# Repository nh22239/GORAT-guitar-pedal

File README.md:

# GORAT RAT clone 
Here at **GORAM** industries, we love the sound of a good dirty **RAT**, but what if we all want to use one at the same time? Suffice to say, we'd probably all get lost in eachothers sound.
That's why we've decided to go custom, a brand new **RAT** clone built by **GORAM**, for **GORAM**.

## New features:
### Frequency response selector switch!

  A simple knob that allows switching the filters of the op-amp stage between **Regular**, **Bass**, and **BEANS** modes
  
### Diode selector switch

  Pick between 6 different diode combinations
  1. BAT41 - BAT 41
  2. Red LED - Red LED 
  3. 1N914 - 1N914
  4. 1N914 - Open
  5. BAT41 - 1N914
  6. BAT41 - Red LED

### Wet/Dry knob
  Does what it says on the tin, for when the un-adulterated bass tone needs to shine through a bit more.

## Future Features:
### Diode selector gain compensation
  When switching diodes, also switch feedback resistor on a compensation op-amp.
### SMD components
  The enclosure is very busy, any new features would probably require this.
### Mini versions
  Much smaller package sizes individualised for Bass, Standard, and Beans.
### Colour LED display
  Switch between red, green, and blue when the feedback capacitor selector is changed, easy to implement as the 4x3 rotarty switch has a free pole but version 1.1 has run out of board space.

## Update 24/03/2026
The PCB's have arrived!
Due to the different heights of components, not to mention mechanical strain, I've designed the board to be printed as one piece that snaps off into three. The intention is that the breakout for the stomp button, and having flying wires for all of the jacks, will reduce the wear on the piece and contribute to a more professional finish.

<?xml version="1.0" encoding="UTF-8" standalone="no"?>
<!-- Created with Inkscape (http://www.inkscape.org/) -->

<svg
   width="210mm"
   height="297mm"
   viewBox="0 0 210 297"
   version="1.1"
   id="svg1"
   xml:space="preserve"
   inkscape:version="1.4.2 (ebf0e94, 2025-05-08)"
   sodipodi:docname="LineDrawing.svg"
   xmlns:inkscape="http://www.inkscape.org/namespaces/inkscape"
   xmlns:sodipodi="http://sodipodi.sourceforge.net/DTD/sodipodi-0.dtd"
   xmlns="http://www.w3.org/2000/svg"
   xmlns:svg="http://www.w3.org/2000/svg"><sodipodi:namedview
     id="namedview1"
     pagecolor="#ffffff"
     bordercolor="#000000"
     borderopacity="0.25"
     inkscape:showpageshadow="2"
     inkscape:pageopacity="0.0"
     inkscape:pagecheckerboard="0"
     inkscape:deskcolor="#d1d1d1"
     inkscape:document-units="mm"
     inkscape:zoom="0.68862935"
     inkscape:cx="238.15424"
     inkscape:cy="382.64416"
     inkscape:window-width="1920"
     inkscape:window-height="991"
     inkscape:window-x="3191"
     inkscape:window-y="435"
     inkscape:window-maximized="1"
     inkscape:current-layer="layer1" /><defs
     id="defs1"><rect
       x="546.73824"
       y="238.45997"
       width="66.79936"
       height="36.65103"
       id="rect40" /><marker
       id="DistanceX"
       orient="auto"
       refX="0.0"
       refY="0.0"
       style="overflow:visible"><path
         d="M 3,-3 L -3,3 M 0,-5 L  0,5"
         style="stroke:#000000; stroke-width:0.5"
         id="path1" /></marker><pattern
       id="Hatch"
       patternUnits="userSpaceOnUse"
       width="8"
       height="8"
       x="0"
       y="0"><path
         d="M8 4 l-4,4"
         stroke="#000000"
         stroke-width="0.25"
         linecap="square"
         id="path2" /><path
         d="M6 2 l-4,4"
         stroke="#000000"
         stroke-width="0.25"
         linecap="square"
         id="path3" /><path
         d="M4 0 l-4,4"
         stroke="#000000"
         stroke-width="0.25"
         linecap="square"
         id="path4" /></pattern><symbol
       id="*MODEL_SPACE" /><symbol
       id="*PAPER_SPACE" /><marker
       id="DistanceX-0"
       orient="auto"
       refX="0.0"
       refY="0.0"
       style="overflow:visible"><path
         d="M 3,-3 L -3,3 M 0,-5 L  0,5"
         style="stroke:#000000; stroke-width:0.5"
         id="path1-9" /></marker><pattern
       id="Hatch-4"
       patternUnits="userSpaceOnUse"
       width="8"
       height="8"
       x="0"
       y="0"><path
         d="M8 4 l-4,4"
         stroke="#000000"
         stroke-width="0.25"
         linecap="square"
         id="path2-8" /><path
         d="M6 2 l-4,4"
         stroke="#000000"
         stroke-width="0.25"
         linecap="square"
         id="path3-8" /><path
         d="M4 0 l-4,4"
         stroke="#000000"
         stroke-width="0.25"
         linecap="square"
         id="path4-2" /></pattern><symbol
       id="*MODEL_SPACE-4" /><symbol
       id="*PAPER_SPACE-5" /><marker
       id="DistanceX-1"
       orient="auto"
       refX="0.0"
       refY="0.0"
       style="overflow:visible"><path
         d="M 3,-3 L -3,3 M 0,-5 L  0,5"
         style="stroke:#000000; stroke-width:0.5"
         id="path1-4" /></marker><pattern
       id="Hatch-2"
       patternUnits="userSpaceOnUse"
       width="8"
       height="8"
       x="0"
       y="0"><path
         d="M8 4 l-4,4"
         stroke="#000000"
         stroke-width="0.25"
         linecap="square"
         id="path2-3" /><path
         d="M6 2 l-4,4"
         stroke="#000000"
         stroke-width="0.25"
         linecap="square"
         id="path3-2" /><path
         d="M4 0 l-4,4"
         stroke="#000000"
         stroke-width="0.25"
         linecap="square"
         id="path4-21" /></pattern><symbol
       id="*MODEL_SPACE-6" /><symbol
       id="*PAPER_SPACE-8" /></defs><g
     inkscape:label="Layer 1"
     inkscape:groupmode="layer"
     id="layer1"><g
       inkscape:label="0"
       id="g13"
       transform="matrix(0.26458333,0,0,-0.26458333,173.01219,290.36032)"><path
         d="m -353.42983,925.10662 a 17.007875,17.007875 0 0 0 -34.01575,0 17.007875,17.007875 0 0 0 34.01575,0 z"
         style="fill:none;stroke:#000000"
         id="path5" /><path
         d="m -211.98102,921.32712 a 26.173228,26.173228 0 0 0 -52.34645,0 26.173228,26.173228 0 0 0 52.34645,0 z"
         style="fill:none;stroke:#000000"
         id="path6" /><path
         d="m -88.862904,925.10662 a 17.007875,17.007875 0 0 0 -34.015746,0 17.007875,17.007875 0 0 0 34.015746,0 z"
         style="fill:none;stroke:#000000"
         id="path7" /><path
         d="M -450.75266,972.35072 H -25.555824 V 870.30342 H -450.75266 Z"
         style="fill:none;stroke:#000000"
         id="path8" /><path
         d="m -450.75266,870.30342 v -11.33855 h 425.196836 v 11.33855 z"
         style="fill:none;stroke:#000000"
         id="path9" /><path
         d="m -450.75266,870.30342 h -11.33859 v 102.0473 h 11.33859 z"
         style="fill:none;stroke:#000000"
         id="path10" /><path
         d="m -450.75266,858.96487 a 11.338583,11.338583 0 0 0 -11.33859,11.33855 h 11.33859 z"
         style="fill:none;stroke:#000000"
         id="path11" /><path
         d="m -25.555824,972.35072 h 11.33859 v -102.0473 h -11.33859 z"
         style="fill:none;stroke:#000000"
         id="path12" /><path
         d="m -25.555824,870.30342 v -11.33855 a 11.338583,11.338583 0 0 1 11.33859,11.33855 z"
         style="fill:none;stroke:#000000"
         id="path13" /></g><g
       inkscape:label="0"
       id="g22"
       transform="matrix(0.26458333,0,0,0.26458333,108.07374,-177.71021)"><path
         d="m 73.322835,1029.8731 a 13.6063,13.6063 0 0 0 -27.212599,0 13.6063,13.6063 0 0 0 27.212599,0 z"
         style="fill:none;stroke:#000000"
         id="path5-5" /><path
         d="m -30.614173,1216.586 a 17.76378,17.76378 0 0 0 -35.527559,0 17.76378,17.76378 0 0 0 35.527559,0 z"
         style="fill:none;stroke:#000000"
         id="path6-1" /><path
         d="m 49.020472,1238.692 a 9.448819,9.448819 0 0 0 -18.897637,0 9.448819,9.448819 0 0 0 18.897637,0 z"
         style="fill:none;stroke:#000000"
         id="path7-7" /><path
         d="m -46.299213,1029.8731 a 13.606299,13.606299 0 0 0 -27.212598,0 13.606299,13.606299 0 0 0 27.212598,0 z"
         style="fill:none;stroke:#000000"
         id="path8-1" /><path
         d="m 192.94488,1028.9283 a 13.6063,13.6063 0 0 0 -27.2126,0 13.6063,13.6063 0 0 0 27.2126,0 z"
         style="fill:none;stroke:#000000"
         id="path9-1" /><path
         d="m -133.36819,1216.586 a 17.76378,17.76378 0 0 0 -35.52756,0 17.76378,17.76378 0 0 0 35.52756,0 z"
         style="fill:none;stroke:#000000"
         id="path10-5" /><path
         d="m 172.40073,1236.0464 a 24.999155,24.999155 0 0 0 -49.99831,0 24.999155,24.999155 0 0 0 49.99831,0 z"
         style="fill:none;stroke:#000000"
         id="path11-2" /><path
         d="m -165.92126,1029.8731 a 13.6063,13.6063 0 0 0 -27.2126,0 13.6063,13.6063 0 0 0 27.2126,0 z"
         style="fill:none;stroke:#000000"
         id="path12-7" /><path
         d="M 212.59842,958.11024 H -212.59842 V 1286.9291 H 212.59842 Z"
         style="fill:none;stroke:#000000"
         id="path13-6" /><path
         d="m 212.59842,946.77165 v 11.33859 h -425.19684 v -11.33859 z"
         style="fill:none;stroke:#000000"
         id="path14" /><path
         d="m -212.59842,946.77165 v 11.33859 h -11.33859 a 11.338583,11.338583 0 0 1 11.33859,-11.33859 z"
         style="fill:none;stroke:#000000"
         id="path15" /><path
         d="m -223.93701,958.11024 h 11.33859 v 328.81886 h -11.33859 z"
         style="fill:none;stroke:#000000"
         id="path16" /><path
         d="m 212.59842,1286.9291 v 11.3386 h -425.19684 v -11.3386 z"
         style="fill:none;stroke:#000000"
         id="path17" /><path
         d="m -212.59842,1286.9291 v 11.3386 a 11.338583,11.338583 0 0 1 -11.33859,-11.3386 z"
         style="fill:none;stroke:#000000"
         id="path18" /><path
         d="m 212.59842,958.11024 h 11.33859 v 328.81886 h -11.33859 z"
         style="fill:none;stroke:#000000"
         id="path19" /><path
         d="m 212.59842,1298.2677 a 11.338583,11.338583 0 0 0 11.33859,-11.3386 h -11.33859 z"
         style="fill:none;stroke:#000000"
         id="path20" /><path
         style="fill:none;stroke:#000000"
         d="M 212.598,946.772 V 958.11"
         id="path21" /><path
         d="m 212.59842,958.11024 h 11.33859 a 11.338583,11.338583 0 0 0 -11.33859,-11.33859 z"
         style="fill:none;stroke:#000000"
         id="path22" /></g><g
       inkscape:label="0"
       id="g10"
       transform="matrix(0,-0.26458333,-0.26458333,0,308.48541,119.99916)"><path
         d="m -164.40945,1107.4016 h 328.8189 v -102.0473 h -328.8189 z"
         style="fill:none;stroke:#000000"
         id="path5-57" /><path
         d="m -164.40945,1005.3543 v -11.33855 h 328.8189 v 11.33855 z"
         style="fill:none;stroke:#000000"
         id="path6-6" /><path
         d="m -164.40945,994.01575 a 11.338583,11.338583 0 0 0 -11.33858,11.33855 h 11.33858 z"
         style="fill:none;stroke:#000000"
         id="path7-1" /><path
         d="m -175.74803,1107.4016 h 11.33858 v -102.0473 h -11.33858 z"
         style="fill:none;stroke:#000000"
         id="path8-8" /><path
         d="m 175.74803,1005.3543 a 11.338583,11.338583 0 0 0 -11.33858,-11.33855 v 11.33855 z"
         style="fill:none;stroke:#000000"
         id="path9-9" /><path
         d="m 164.40945,1107.4016 h 11.33858 v -102.0473 h -11.33858 z"
         style="fill:none;stroke:#000000"
         id="path10-2" /></g><g
       inkscape:label="0"
       id="g28"
       transform="matrix(0,0.26458333,0.26458333,0,-92.15514,118.58116)"><path
         d="m -164.40945,1107.4016 h 328.8189 v -102.0473 h -328.8189 z"
         style="fill:none;stroke:#000000"
         id="path23" /><path
         d="m -164.40945,1005.3543 v -11.33855 h 328.8189 v 11.33855 z"
         style="fill:none;stroke:#000000"
         id="path24" /><path
         d="m -164.40945,994.01575 a 11.338583,11.338583 0 0 0 -11.33858,11.33855 h 11.33858 z"
         style="fill:none;stroke:#000000"
         id="path25" /><path
         d="m -175.74803,1107.4016 h 11.33858 v -102.0473 h -11.33858 z"
         style="fill:none;stroke:#000000"
         id="path26" /><path
         d="m 175.74803,1005.3543 a 11.338583,11.338583 0 0 0 -11.33858,-11.33855 v 11.33855 z"
         style="fill:none;stroke:#000000"
         id="path27" /><path
         d="m 164.40945,1107.4016 h 11.33858 v -102.0473 h -11.33858 z"
         style="fill:none;stroke:#000000"
         id="path28" /></g><g
       id="g37"
       transform="translate(0,8.4527814)"><path
         d="M 51.82946,206.78981 H 164.32945 V 179.7898 H 51.82946 Z"
         style="fill:none;stroke:#000000;stroke-width:0.264583"
         id="path32" /><path
         d="m 51.82946,179.7898 v -2.99999 h 112.49999 v 2.99999 z"
         style="fill:none;stroke:#000000;stroke-width:0.264583"
         id="path33" /><path
         d="m 51.82946,179.7898 h -3.000002 v 27.00001 h 3.000002 z"
         style="fill:none;stroke:#000000;stroke-width:0.264583"
         id="path34" /><path
         d="m 51.82946,176.78981 a 3,3 0 0 0 -3.000002,2.99999 h 3.000002 z"
         style="fill:none;stroke:#000000;stroke-width:0.264583"
         id="path35" /><path
         d="m 164.32945,206.78981 h 3.00001 V 179.7898 h -3.00001 z"
         style="fill:none;stroke:#000000;stroke-width:0.264583"
         id="path36" /><path
         d="m 164.32945,179.7898 v -2.99999 a 3,3 0 0 1 3.00001,2.99999 z"
         style="fill:none;stroke:#000000;stroke-width:0.264583"
         id="path37" /></g><text
       xml:space="preserve"
       style="font-size:4.9389px;line-height:1;font-family:Typewriter-Serial;-inkscape-font-specification:'Typewriter-Serial, Normal';text-align:center;writing-mode:lr-tb;direction:ltr;text-anchor:middle;white-space:pre;inline-size:24.3507;fill:#000000;stroke-width:0.365001;stroke-linejoin:round;paint-order:markers stroke fill"
       x="51.823742"
       y="72.78978"
       id="text37"
       transform="translate(7.6071151,-2.7168268)"><tspan
         x="51.823742"
         y="72.78978"
         id="tspan2"><tspan
           style="stroke-width:0.365"
           id="tspan1">Gain</tspan></tspan></text><text
       xml:space="preserve"
       style="font-size:4.9389px;line-height:1;font-family:Typewriter-Serial;-inkscape-font-specification:'Typewriter-Serial, Normal';text-align:center;writing-mode:lr-tb;direction:ltr;text-anchor:middle;white-space:pre;inline-size:24.3507;fill:#000000;stroke-width:0.365001;stroke-linejoin:round;paint-order:markers stroke fill"
       x="51.823742"
       y="72.78978"
       id="text38"
       transform="translate(39.937354,-2.9885095)"><tspan
         x="51.823742"
         y="72.78978"
         id="tspan4"><tspan
           style="stroke-width:0.365"
           id="tspan3">Filter</tspan></tspan></text><text
       xml:space="preserve"
       style="font-size:4.9389px;line-height:1;font-family:Typewriter-Serial;-inkscape-font-specification:'Typewriter-Serial, Normal';text-align:center;writing-mode:lr-tb;direction:ltr;text-anchor:middle;white-space:pre;inline-size:24.3507;fill:#000000;stroke-width:0.365001;stroke-linejoin:round;paint-order:markers stroke fill"
       x="51.823742"
       y="72.78978"
       id="text39"
       transform="translate(71.251067,-3.3727268)"><tspan
         x="51.823742"
         y="72.78978"
         id="tspan6"><tspan
           style="stroke-width:0.365"
           id="tspan5">Volume</tspan></tspan></text><text
       xml:space="preserve"
       transform="scale(0.26458333)"
       id="text40"
       style="text-orientation:auto;stroke-linejoin:round;-inkscape-font-specification:'Typewriter-Serial, Normal';font-family:Typewriter-Serial;font-size:18.66666667px;fill:#000000;line-height:1;paint-order:markers stroke fill;stroke-width:1.37952756;text-align:center;writing-mode:lr-tb;direction:ltr;white-space:pre;shape-inside:url(#rect40)" /><text
       xml:space="preserve"
       style="font-size:4.9389px;line-height:1;font-family:Typewriter-Serial;-inkscape-font-specification:'Typewriter-Serial, Normal';text-align:center;writing-mode:lr-tb;direction:ltr;text-anchor:middle;white-space:pre;inline-size:24.3507;fill:#000000;stroke-width:0.365001;stroke-linejoin:round;paint-order:markers stroke fill"
       x="51.823742"
       y="72.78978"
       id="text41"
       transform="translate(102.37267,-3.3727268)"><tspan
         x="51.823742"
         y="72.78978"
         id="tspan8"><tspan
           style="stroke-width:0.365"
           id="tspan7">Wet/Dry</tspan></tspan></text><text
       xml:space="preserve"
       style="font-size:4.9389px;line-height:1;font-family:Typewriter-Serial;-inkscape-font-specification:'Typewriter-Serial, Normal';text-align:center;writing-mode:lr-tb;direction:ltr;text-anchor:middle;white-space:pre;inline-size:24.3507;fill:#000000;stroke-width:0.365001;stroke-linejoin:round;paint-order:markers stroke fill"
       x="51.823742"
       y="72.78978"
       id="text42"
       transform="translate(14.194792,99.213302)"><tspan
         x="51.823742"
         y="72.78978"
         id="tspan10"><tspan
           style="stroke-width:0.365"
           id="tspan9">Bass/</tspan></tspan><tspan
         x="51.823742"
         y="77.728687"
         id="tspan12"><tspan
           style="stroke-width:0.365"
           id="tspan11">Reg/</tspan></tspan><tspan
         x="51.823742"
         y="82.667591"
         id="tspan14"><tspan
           style="stroke-width:0.365"
           id="tspan13">Beans</tspan></tspan></text><text
       xml:space="preserve"
       style="font-size:4.9389px;line-height:1;font-family:Typewriter-Serial;-inkscape-font-specification:'Typewriter-Serial, Normal';text-align:center;writing-mode:lr-tb;direction:ltr;text-anchor:middle;white-space:pre;inline-size:24.3507;fill:#000000;stroke-width:0.365001;stroke-linejoin:round;paint-order:markers stroke fill"
       x="51.823742"
       y="72.78978"
       id="text43"
       transform="translate(43.011092,99.789628)"><tspan
         x="51.823742"
         y="72.78978"
         id="tspan16"><tspan
           style="stroke-width:0.365"
           id="tspan15">Diode</tspan><tspan
           y="72.78978"
           id="tspan17"> </tspan></tspan><tspan
         x="51.823742"
         y="77.728687"
         id="tspan19"><tspan
           style="stroke-width:0.365"
           id="tspan18">Selection</tspan></tspan></text><text
       xml:space="preserve"
       style="font-size:4.9389px;line-height:1;font-family:Typewriter-Serial;-inkscape-font-specification:'Typewriter-Serial, Normal';text-align:center;writing-mode:lr-tb;direction:ltr;text-anchor:middle;white-space:pre;inline-size:24.3507;fill:#000000;stroke-width:0.365001;stroke-linejoin:round;paint-order:markers stroke fill"
       x="51.823742"
       y="72.78978"
       id="text44"
       transform="translate(70.866849,99.789628)"><tspan
         x="51.823742"
         y="72.78978"
         id="tspan21"><tspan
           style="stroke-width:0.365"
           id="tspan20">LED</tspan></tspan></text><text
       xml:space="preserve"
       style="font-size:4.9389px;line-height:1;font-family:Typewriter-Serial;-inkscape-font-specification:'Typewriter-Serial, Normal';text-align:center;writing-mode:lr-tb;direction:ltr;text-anchor:middle;white-space:pre;inline-size:34.7246;fill:#000000;stroke-width:0.365001;stroke-linejoin:round;paint-order:markers stroke fill"
       x="51.823742"
       y="72.78978"
       id="text45"
       transform="translate(95.26465,102.47915)"><tspan
         x="51.823742"
         y="72.78978"
         id="tspan23"><tspan
           style="stroke-width:0.365"
           id="tspan22">Footswitch</tspan></tspan></text><text
       xml:space="preserve"
       style="font-size:4.9389px;line-height:1;font-family:Typewriter-Serial;-inkscape-font-specification:'Typewriter-Serial, Normal';text-align:center;writing-mode:lr-tb;direction:ltr;text-anchor:middle;white-space:pre;inline-size:34.7246;fill:#000000;stroke-width:0.365001;stroke-linejoin:round;paint-order:markers stroke fill"
       x="51.823742"
       y="72.78978"
       id="text46"
       transform="translate(96.108218,-44.483981)"><tspan
         x="51.823742"
         y="72.78978"
         id="tspan25"><tspan
           style="stroke-width:0.365"
           id="tspan24">In</tspan></tspan></text><text
       xml:space="preserve"
       style="font-size:4.9389px;line-height:1;font-family:Typewriter-Serial;-inkscape-font-specification:'Typewriter-Serial, Normal';text-align:center;writing-mode:lr-tb;direction:ltr;text-anchor:middle;white-space:pre;inline-size:34.7246;fill:#000000;stroke-width:0.365001;stroke-linejoin:round;paint-order:markers stroke fill"
       x="51.823742"
       y="72.78978"
       id="text47"
       transform="translate(22.914816,-46.02085)"><tspan
         x="51.823742"
         y="72.78978"
         id="tspan27"><tspan
           style="stroke-width:0.365"
           id="tspan26">Out</tspan></tspan></text></g></svg>

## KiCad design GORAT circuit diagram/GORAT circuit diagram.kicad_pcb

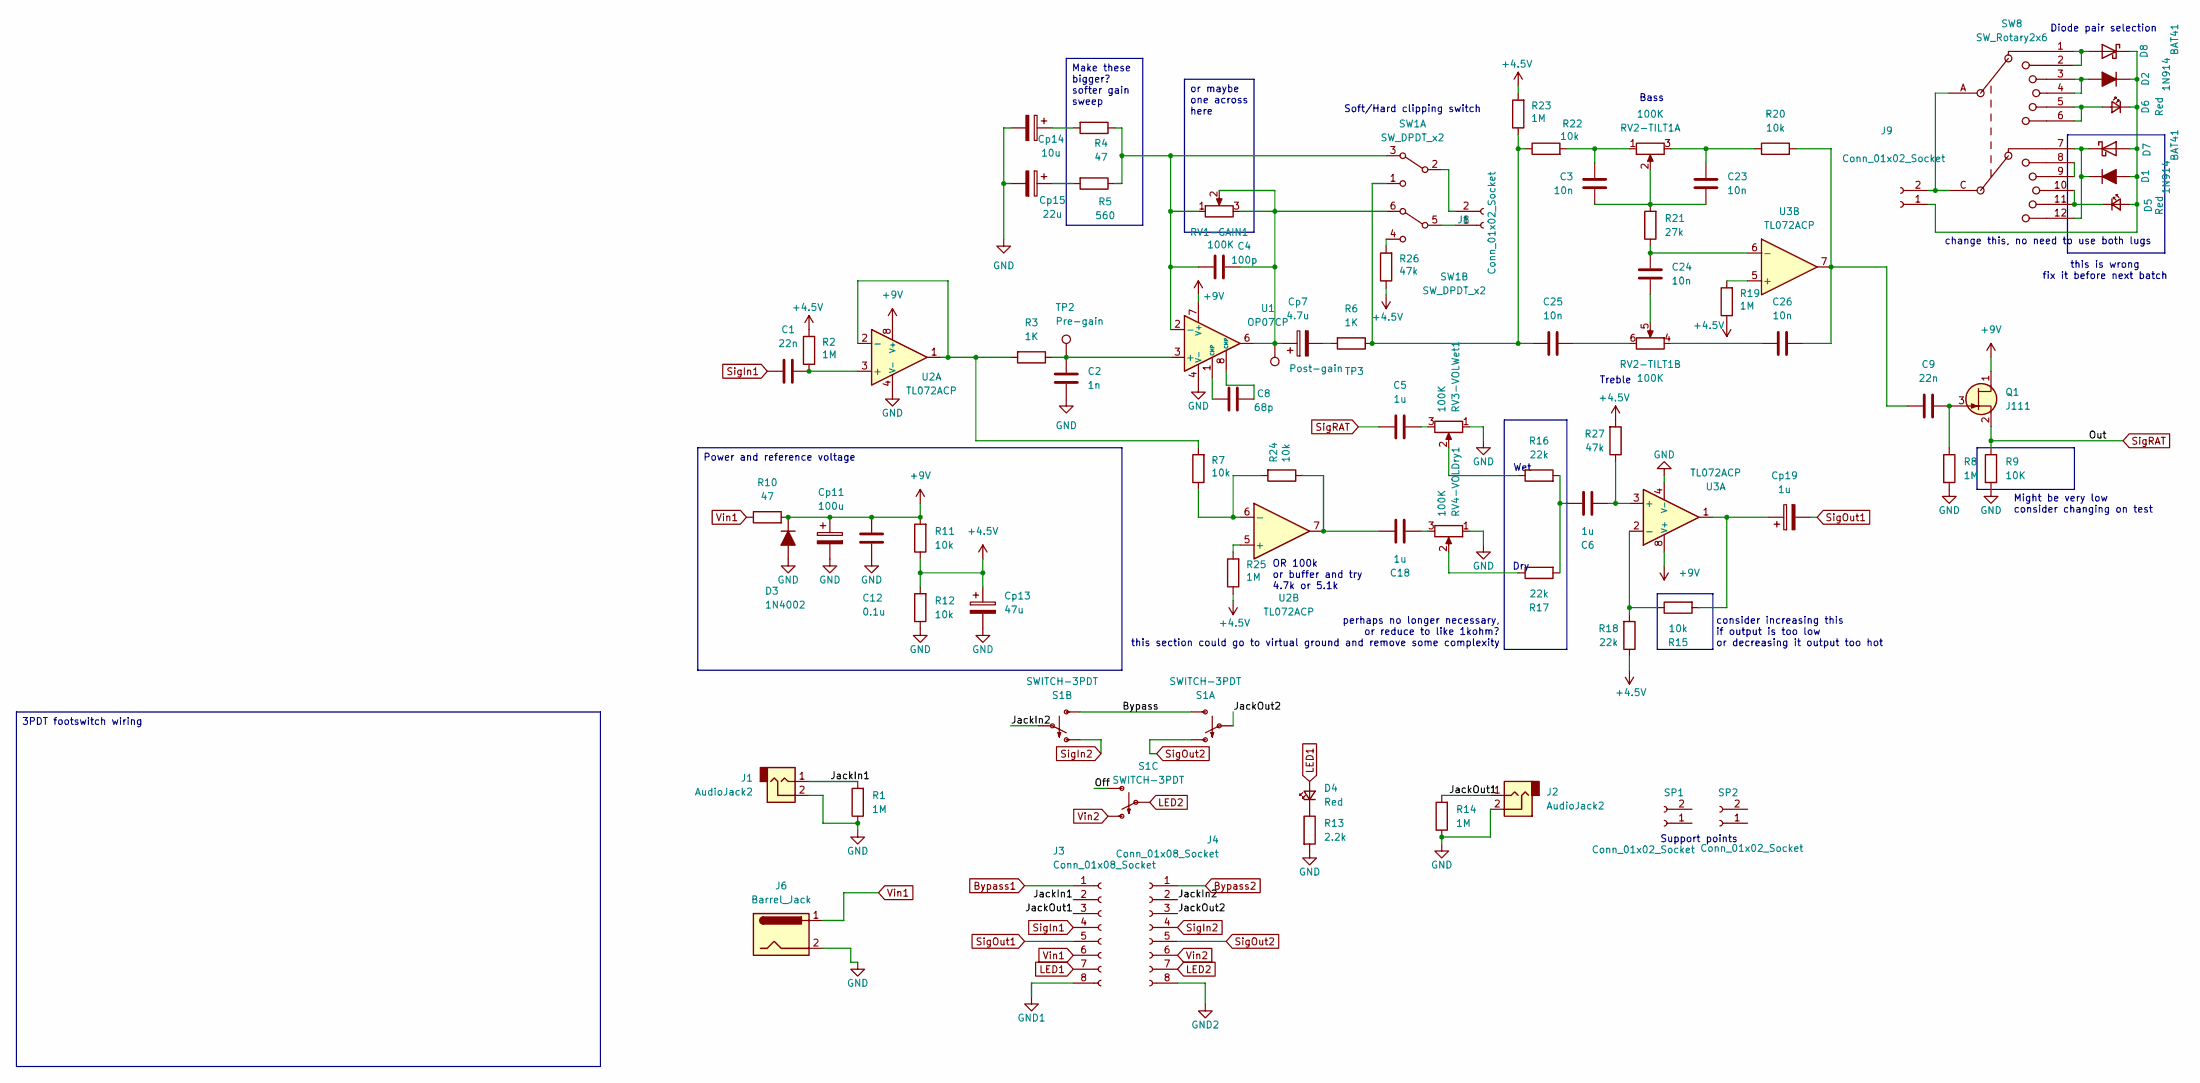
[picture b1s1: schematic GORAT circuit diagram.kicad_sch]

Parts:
C1, C9: 22n; C_Disc_D4.7mm_W2.5mm_P5.00mm
C2: 1n; C_Disc_D4.7mm_W2.5mm_P5.00mm
C3, C23, C24, C25, C26: 10n; C_Disc_D4.7mm_W2.5mm_P5.00mm
C4: 100p; C_Disc_D4.7mm_W2.5mm_P5.00mm
C5, C6, C18: 1u; C_Disc_D4.7mm_W2.5mm_P5.00mm
C8: 68p; C_Disc_D4.7mm_W2.5mm_P5.00mm
C12: 0.1u; C_Disc_D4.7mm_W2.5mm_P5.00mm
Cp7: 4.7u; CP_Radial_D5.0mm_P2.50mm
Cp11: 100u; CP_Radial_D5.0mm_P2.50mm
Cp13: 47u; CP_Radial_D5.0mm_P2.50mm
Cp14: 10u; CP_Radial_D5.0mm_P2.50mm
Cp15: 22u; CP_Radial_D5.0mm_P2.50mm
Cp19: 1u; CP_Radial_D5.0mm_P2.50mm
D1, D2: 1N914; D_DO-35_SOD27_P7.62mm_Horizontal
D3: 1N4002; D_DO-41_SOD81_P7.62mm_Horizontal
D4: Red; LED_D5.0mm
D5, D6: Red; LED_D3.0mm
D7, D8: BAT41; D_DO-35_SOD27_P7.62mm_Horizontal
J1, J2: AudioJack2; SolderWire-0.75sqmm_1x02_P7mm_D1.25mm_OD3.5mm
J3, J4: Conn_01x08_Socket; PinHeader_1x08_P2.54mm_Vertical
J6: Barrel_Jack; SolderWire-0.5sqmm_1x02_P4.6mm_D0.9mm_OD2.1mm
J8, J9: Conn_01x02_Socket; PinHeader_1x02_P2.54mm_Vertical
Q1: J111; TO-92_Inline_Wide_DSG
R1, R2, R8, R14, R19, R23, R25: 1M; R_Axial_DIN0207_L6.3mm_D2.5mm_P10.16mm_Horizontal
R3, R6: 1K; R_Axial_DIN0207_L6.3mm_D2.5mm_P10.16mm_Horizontal
R4, R10: 47; R_Axial_DIN0207_L6.3mm_D2.5mm_P10.16mm_Horizontal
R5: 560; R_Axial_DIN0207_L6.3mm_D2.5mm_P10.16mm_Horizontal
R7, R11, R12, R15, R20, R22, R24: 10k; R_Axial_DIN0207_L6.3mm_D2.5mm_P10.16mm_Horizontal
R9: 10K; R_Axial_DIN0207_L6.3mm_D2.5mm_P10.16mm_Horizontal
R13: 2.2k; R_Axial_DIN0207_L6.3mm_D2.5mm_P10.16mm_Horizontal
R16, R17, R18: 22k; R_Axial_DIN0207_L6.3mm_D2.5mm_P10.16mm_Horizontal
R21: 27k; R_Axial_DIN0207_L6.3mm_D2.5mm_P10.16mm_Horizontal
R26, R27: 47k; R_Axial_DIN0207_L6.3mm_D2.5mm_P10.16mm_Horizontal
RV1-GAIN1, RV3-VOLWet1, RV4-VOLDry1: 100K; Potentiometer_Alpha_RD901F-40-00D_Single_Vertical
RV2-TILT1: 100K; Potentiometer_Alpha_RD902F-40-00D_Dual_Vertical
S1: SWITCH-3PDT; 3PDT_fixed
SP1, SP2: Conn_01x02_Socket; PinHeader_1x02_P2.54mm_Vertical
SW1: SW_DPDT_x2; DPDT_fixed
SW8: SW_Rotary2x6; RS26
TP2: Pre-gain; TestPoint_Pad_D2.0mm
TP3: Post-gain; TestPoint_Pad_D2.0mm
U1: OP07CP; DIP-8_W7.62mm_LongPads
U2, U3: TL072ACP; DIP-8_W7.62mm_LongPads

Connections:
+4.5V: Cp13.1, R2.2, R11.1, R12.2, R18.1, R19.1, R23.2, R25.1, R26.1, R27.2
+9V: C12.2, Cp11.1, D3.1 (K), Q1.1 (D), R10.2, R11.2, U1.7 (V+), U2.8 (V+), U3.8 (V+)
/Bypass: S1.P$3 (S), S1.P$6 (S)
/JackIn1: J1.1, J3.2, R1.2
/JackIn2: J4.2, S1.P$5
/JackOut1: J2.1, J3.3, R14.2
/JackOut2: J4.3, S1.P$2
/Off: S1.P$9 (S)
Bypass1: J3.1
Bypass2: J4.1
GND: C2.1, C12.1, Cp11.2, Cp13.2, Cp14.2, Cp15.2, D3.2 (A), J1.2, J2.2, J6.2, R1.1, R8.2, R9.2, R12.1, R13.2, R14.1, RV3-VOLWet1.1, RV4-VOLDry1.1, U1.4 (V-), U2.4 (V-), U3.4 (V-)
GND1: J3.8
GND2: J4.8
LED1: D4.2 (A), J3.7
LED2: J4.7, S1.P$8
unnamed: C3.2, R22.2, RV2-TILT1.1
unnamed: C5.2, RV3-VOLWet1.3
unnamed: C6.1, R16.2, R17.2
unnamed: C8.1, U1.1 (CMP)
unnamed: C8.2, U1.8 (CMP)
unnamed: C18.1, R24.1, U2.7
unnamed: C18.2, RV4-VOLDry1.3
unnamed: C3.1, C23.1, R21.2, RV2-TILT1.2
unnamed: C23.2, R20.1, RV2-TILT1.3
unnamed: C24.1, RV2-TILT1.5
unnamed: C25.1, RV2-TILT1.6
unnamed: C9.2, C26.1, R20.2, U3.7
unnamed: C26.2, RV2-TILT1.4
unnamed: Cp7.2, R6.2
unnamed: Cp14.1, R4.2
unnamed: Cp15.1, R5.2
unnamed: Cp19.1, R15.2, U3.1
unnamed: D1.2 (A), D2.1 (K), D5.2 (A), D6.1 (K), D7.2 (A), D8.1 (K), J9.1
unnamed: D1.1 (K), D7.1 (K), SW8.7, SW8.12
unnamed: D2.2 (A), SW8.3, SW8.4
unnamed: D4.1 (K), R13.1
unnamed: D5.1 (K), SW8.10, SW8.11
unnamed: D6.2 (A), SW8.5, SW8.6
unnamed: D8.2 (A), SW8.1, SW8.2
unnamed: J8.1, SW1.5 (B)
unnamed: J8.2, SW1.2 (B)
unnamed: J9.2, SW8.A, SW8.C
unnamed: C9.1, Q1.3 (G), R8.1
unnamed: R16.1, RV3-VOLWet1.2
unnamed: R17.1, RV4-VOLDry1.2
unnamed: C25.2, R6.1, R22.1, R23.1, SW1.1 (A)
unnamed: C4.2, R4.1, R5.1, RV1-GAIN1.1, SW1.3 (C), U1.2 (-)
unnamed: R26.2, SW1.4 (A)
unnamed: C4.1, Cp7.1, RV1-GAIN1.2, RV1-GAIN1.3, SW1.6 (C), TP3.1, U1.6
unnamed: SW8.8, SW8.9
unnamed: C2.2, R3.1, TP2.1, U1.3 (+)
unnamed: C1.2, R2.1, U2.3 (+)
unnamed: R3.2, R7.2, U2.1, U2.2 (-)
unnamed: R25.2, U2.5 (+)
unnamed: R7.1, R24.2, U2.6 (-)
unnamed: C6.2, R27.1, U3.3 (+)
unnamed: R15.1, R18.2, U3.2 (-)
unnamed: R19.2, U3.5 (+)
unnamed: C24.2, R21.1, U3.6 (-)
SigIn1: C1.1, J3.4
SigIn2: J4.4, S1.P$4 (O)
SigOut1: Cp19.2, J3.5
SigOut2: J4.5, S1.P$1 (O)
SigRAT: C5.1, Q1.2 (S), R9.1
Vin1: J3.6, J6.1, R10.1
Vin2: J4.6, S1.P$7 (O)

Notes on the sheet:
Wet
OR 100k or buffer and try 4.7k or 5.1k
Might be very low consider changing on test
Soft/Hard clipping switch
consider increasing this if output is too low or decreasing it output too hot
change this, no need to use both lugs
Treble
Support points
Bass
perhaps no longer necessary, or reduce to like 1kohm? this section could go to virtual ground and remove some complexity
Diode pair selection
Dry
this is wrong fix it before next batch
or maybe one across here
Make these bigger? softer gain sweep
3PDT footswitch wiring
Power and reference voltage

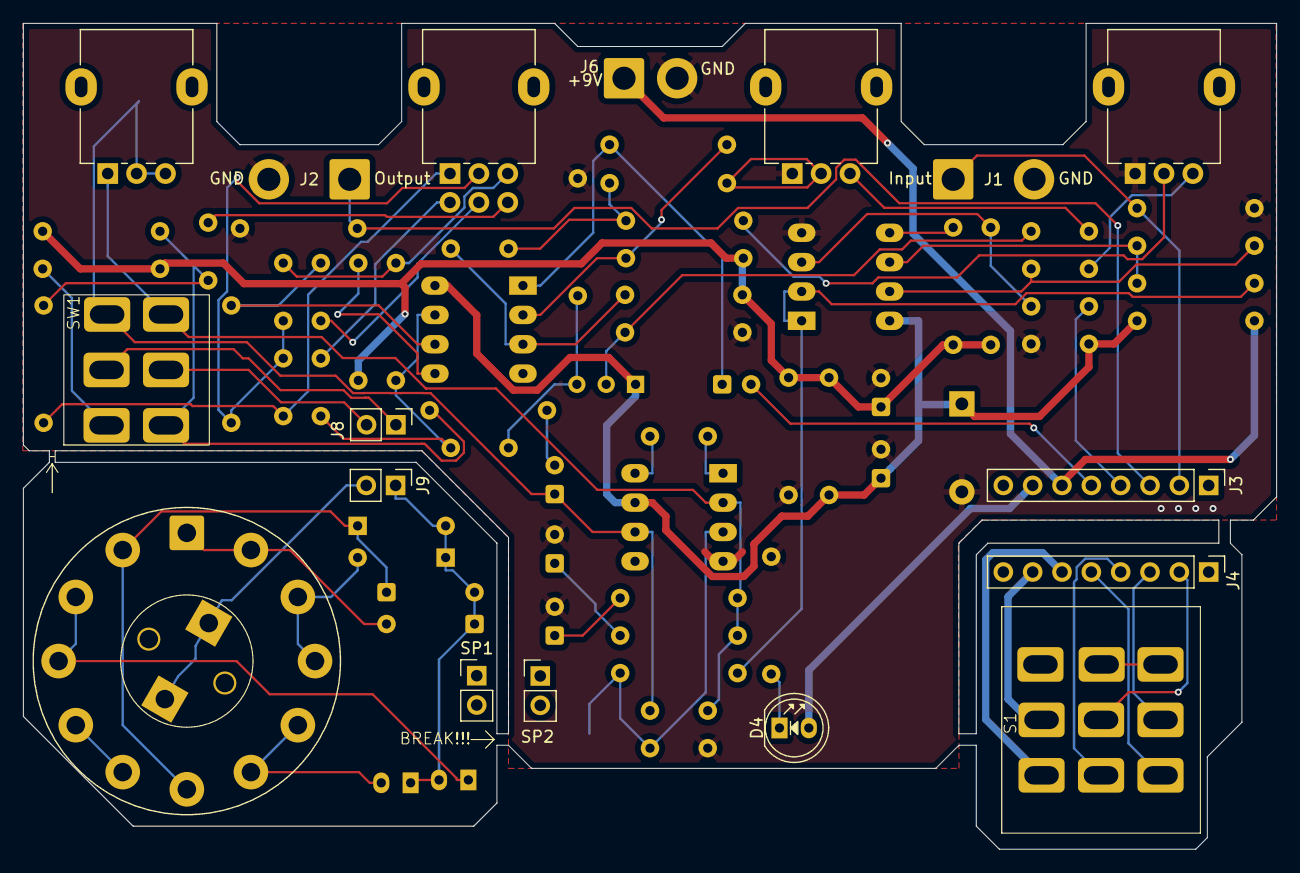
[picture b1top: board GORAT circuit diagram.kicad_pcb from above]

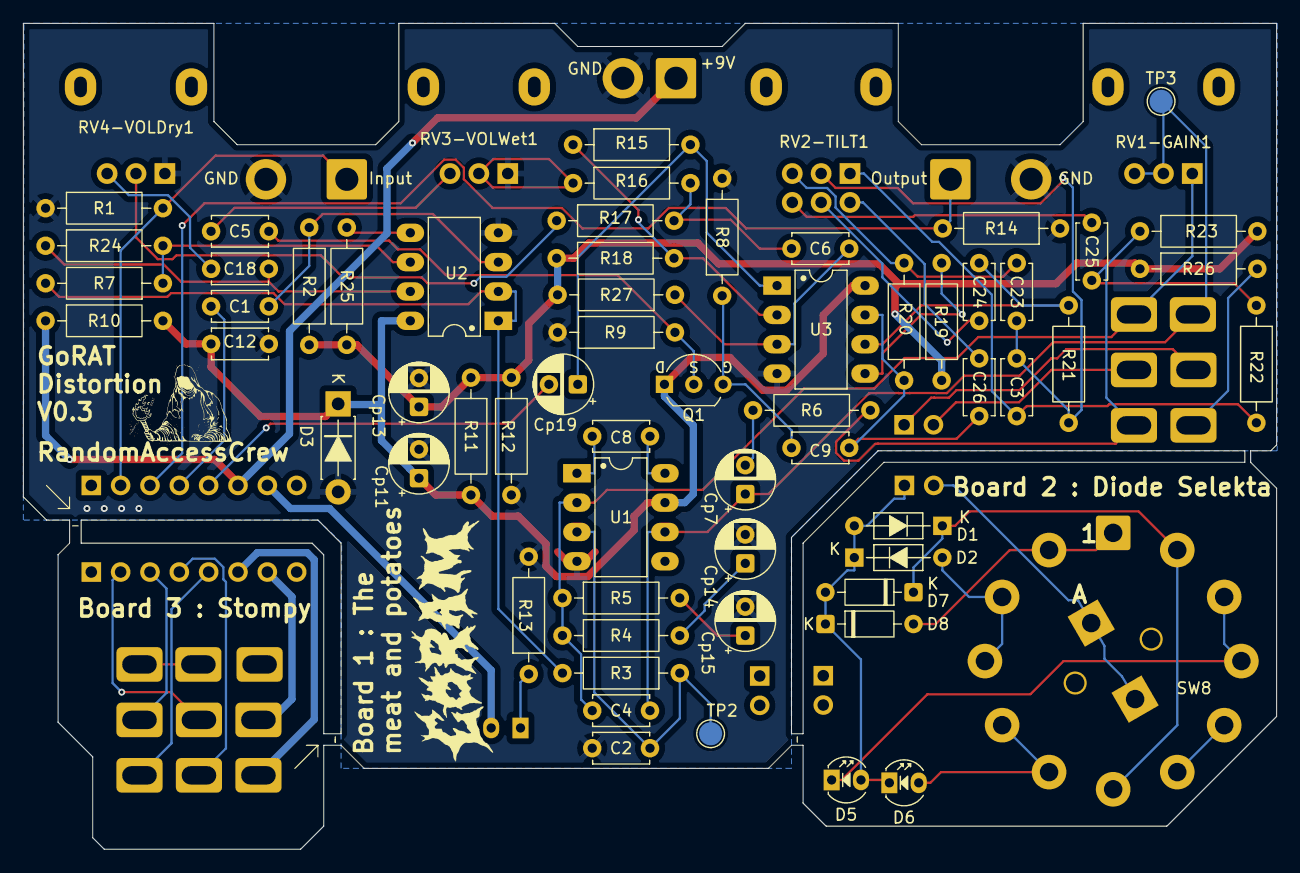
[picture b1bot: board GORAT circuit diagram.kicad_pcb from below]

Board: 2 copper layers, 108.5 x 71.5 mm, 77 parts (60 on the bottom side), 61 nets.

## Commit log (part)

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2026-02-17 Add KiCad project files for GORAT circuit
    Initial import of the GORAT guitar pedal KiCad project. Adds schematic (.kicad_sch), PCB (.kicad_pcb), project file (.kicad_pro), project preferences (.kicad_prl), fp-info-cache, autosave/lock file a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
2026-02-19 Add ngspice support and schematic backups
    Enable ngspice in the KiCad project and update the schematic for simulation: add ngspice config and workbook in .kicad_pro; replace/extend power symbols with Simulation_SPICE VDC/VSIN symbols and sim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
2026-02-19 Revise branding in README description
    Updated README to emphasize GORAM branding.
2026-02-19 Fix quotation marks in README.md
2026-02-19 Enhance README formatting for clarity
    Updated README to emphasize GORAM and RAT with bold formatting.
2026-02-19 Format feature description in README.md
2026-03-02 Update KiCad PCB and add backups
    Replace GORAT circuit diagram.kicad_pcb with the full PCB data (expanded footprints, nets, layers and layout). Update related project files (GORAT circuit diagram.kicad_pro, .kicad_sch and fp-info-ca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
2026-03-03 asdsa
2026-03-09 Update README to improve formatting of features section
2026-03-09 almost done
2026-03-11 close to done
2026-03-11 Update KiCad PCB, add backups and artwork
    Modify GORAT circuit diagram.kicad_pcb: reorder/renumber nets, adjust several pad/net assignments and component positions, and add numerous F.Fab properties (Availability, Check_prices, Description_1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
2026-03-12 Enhance README with diode options and future features
    Added future features section and expanded diode selector details.
2026-03-12 Update README with formatted future features
2026-03-12 Add line drawing image to README
    Added a line drawing image to the README.
2026-03-12 Add Colour LED display feature to README
    Added a section about the Colour LED display feature.
2026-03-18 Update disc capacitor footprints and BOM
    Replace THT disc capacitor footprints with smaller C_Disc_D4.7mm_W2.5mm variants across schematic and PCB (updated 3D model paths, silk/text positions, rotations and UUIDs). Update project metadata: 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
2026-03-20 BOM work
2026-03-24 Add PCB delivery update to README
    Added update section with PCB delivery details and images.
2026-03-24 Fix formatting and update PCB design details
    Corrected formatting for the update section and added details about the PCB design.
2026-03-24 Remove PCB delivery image from README
    Removed the PCB delivery image from the README.
2026-03-24 Add PCB delivery image to README
    Added an image of the PCB delivery to the README.
2026-03-24 fixed silk screen errors
2026-03-24 Update KiCad PCB, add build guide & backups
    Apply multiple updates to the GoRAT project: modify the KiCad PCB (footprint/pad geometry, silkscreen labels, routing segments and UUIDs), and update accompanying KiCad project files and the GoRAT sp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
2026-03-25 begun bass version
2026-03-26 Fixed disconnection issue
2026-03-31 fixed issues
2026-04-01 Update GORAT KiCad PCB, schematics & backups
    Modify KiCad project files and update backup archives. Changes include:
    - Updated Build_Guide.docx (binary change).
    - Removed several older GORAT backup ZIPs and added new backups dated 2026-04-01.
    - Extensive edits to GORAT circuit diagram.kicad_pcb: net renumbering/reassignments, footprint position adjustments, pad/net fixes, updated pad/net mappings, many UUID/fp_line/fp_poly/attribute adjus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
    - Minor updates to GORAT circuit diagram.kicad_prl, .kicad_sch and fp-info-cache.
    These changes appear to realign component placements and correct net assignments in the PCB while refreshing project backup
2026-04-01 Update KiCad schematic positions and prefs
    Enable additional selection filters in GORAT circuit diagram.kicad_prl (dimensions, footprints, graphics, keepouts, otherItems, pads, text, vias, zones) to improve editing. Adjust many coordinates in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
2026-04-02 Update KiCad schematic and PCB to v1.3
    Add new KiCad schematic 'GORAT circuit diagram 1.3.kicad_sch' and v1.3 PCB/project files; modify existing GORAT schematic, PCB (.kicad_pcb) and project library (.kicad_prl). Add multiple backup ZIP a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
2026-04-06 Adjust KiCad schematic junctions and wires
    Rearranged junctions and wires in GORAT circuit diagram.kicad_sch to correct routing and updated related UUIDs; also moved several diode symbol positions (D1, D2, D7, D8). Added two new schematic bac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
2026-04-10 Update Build_Guide and add GORAT backup zip
    Update Build_Guide.docx (documentation changes) and add a new backup ZIP for the GORAT circuit diagram: GORAT circuit diagram-2026-04-04_053106.zip under the backups folder.
2026-04-13 potentially fixed volume mixer
2026-04-13 Schematic: add +5V, C6, R27; adjust wires
    Added a +5V power symbol, C6 (1u) and R27 (47k); adjusted component positions, junctions and wire routing to match the new connections. Updated a resistor value from 100k to 10k and corrected several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
2026-04-14 update board and layout
2026-04-14 Update KiCad files: remap nets and rename caps
    Synchronise PCB and schematic: remap many net indices across GORAT circuit diagram (.kicad_pcb, .kicad_sch, .kicad_prl, .kicad_pro) to match the schematic, and rename several capacitor references (e.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
2026-04-14 Add net color definitions and remove PCB lockfile
    Set net color mappings in the KiCad project file for +4.5V and +9V nets to make them visually distinct. Also remove the transient PCB lock file (~GORAT circuit diagram.kicad_pcb.lck) that contained h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
2026-04-15 Add GoRAT schematic files; update SVG layout
    Add GoRATv0.2.xlsx and a circuit-diagram backup zip. Modify GoRAT_pedal_1590BB_TechnicalDrawing.svg to change canvas size/orientation (viewBox and width/height), update Inkscape document metadata (zo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
2026-04-24 V0.2 finished
